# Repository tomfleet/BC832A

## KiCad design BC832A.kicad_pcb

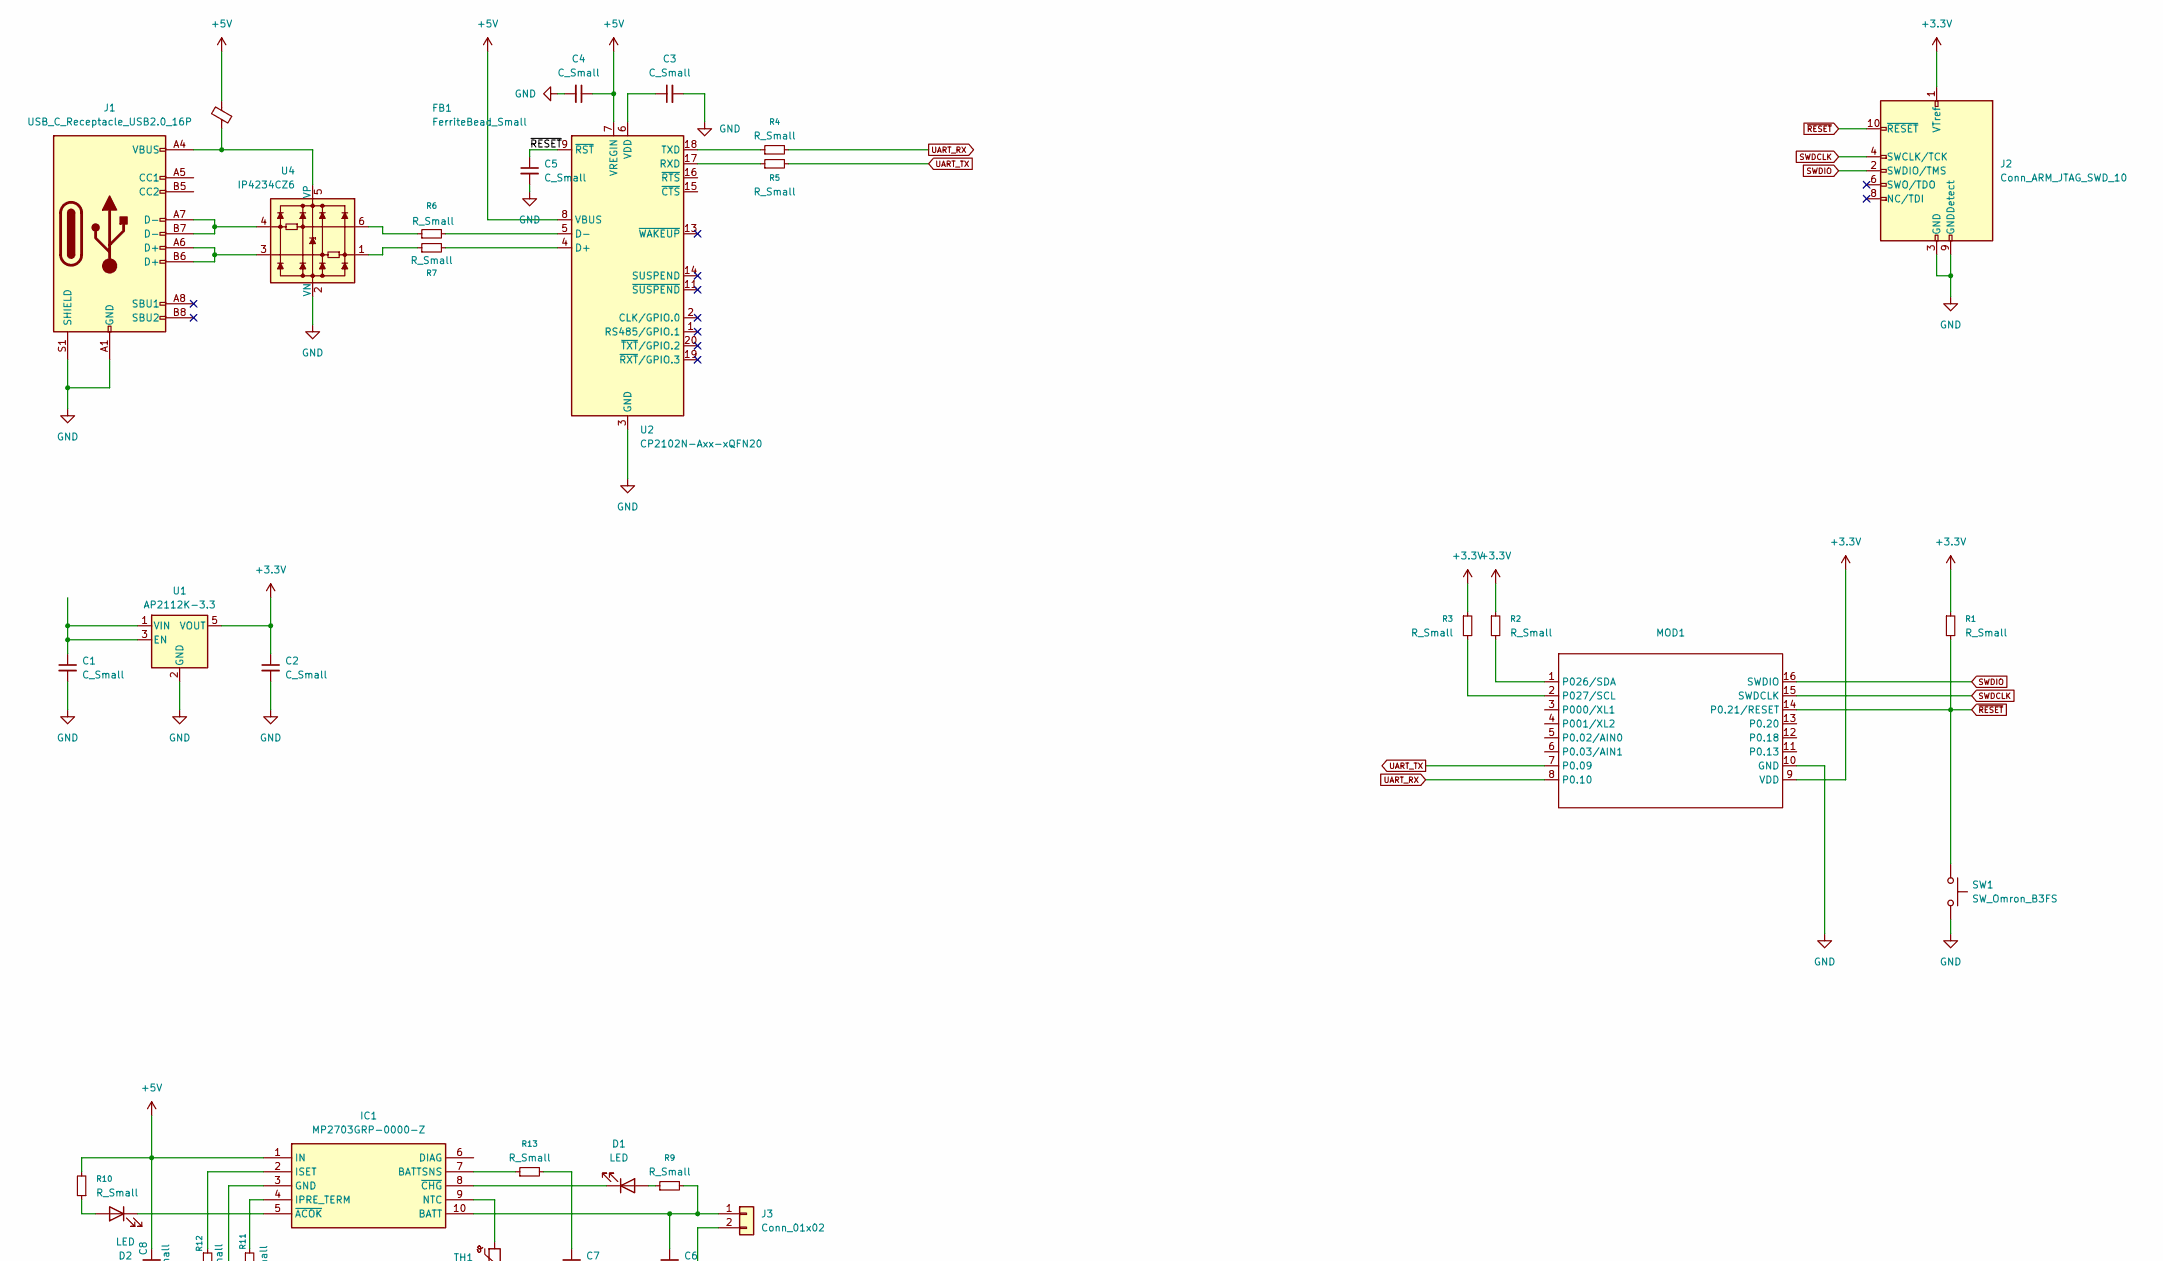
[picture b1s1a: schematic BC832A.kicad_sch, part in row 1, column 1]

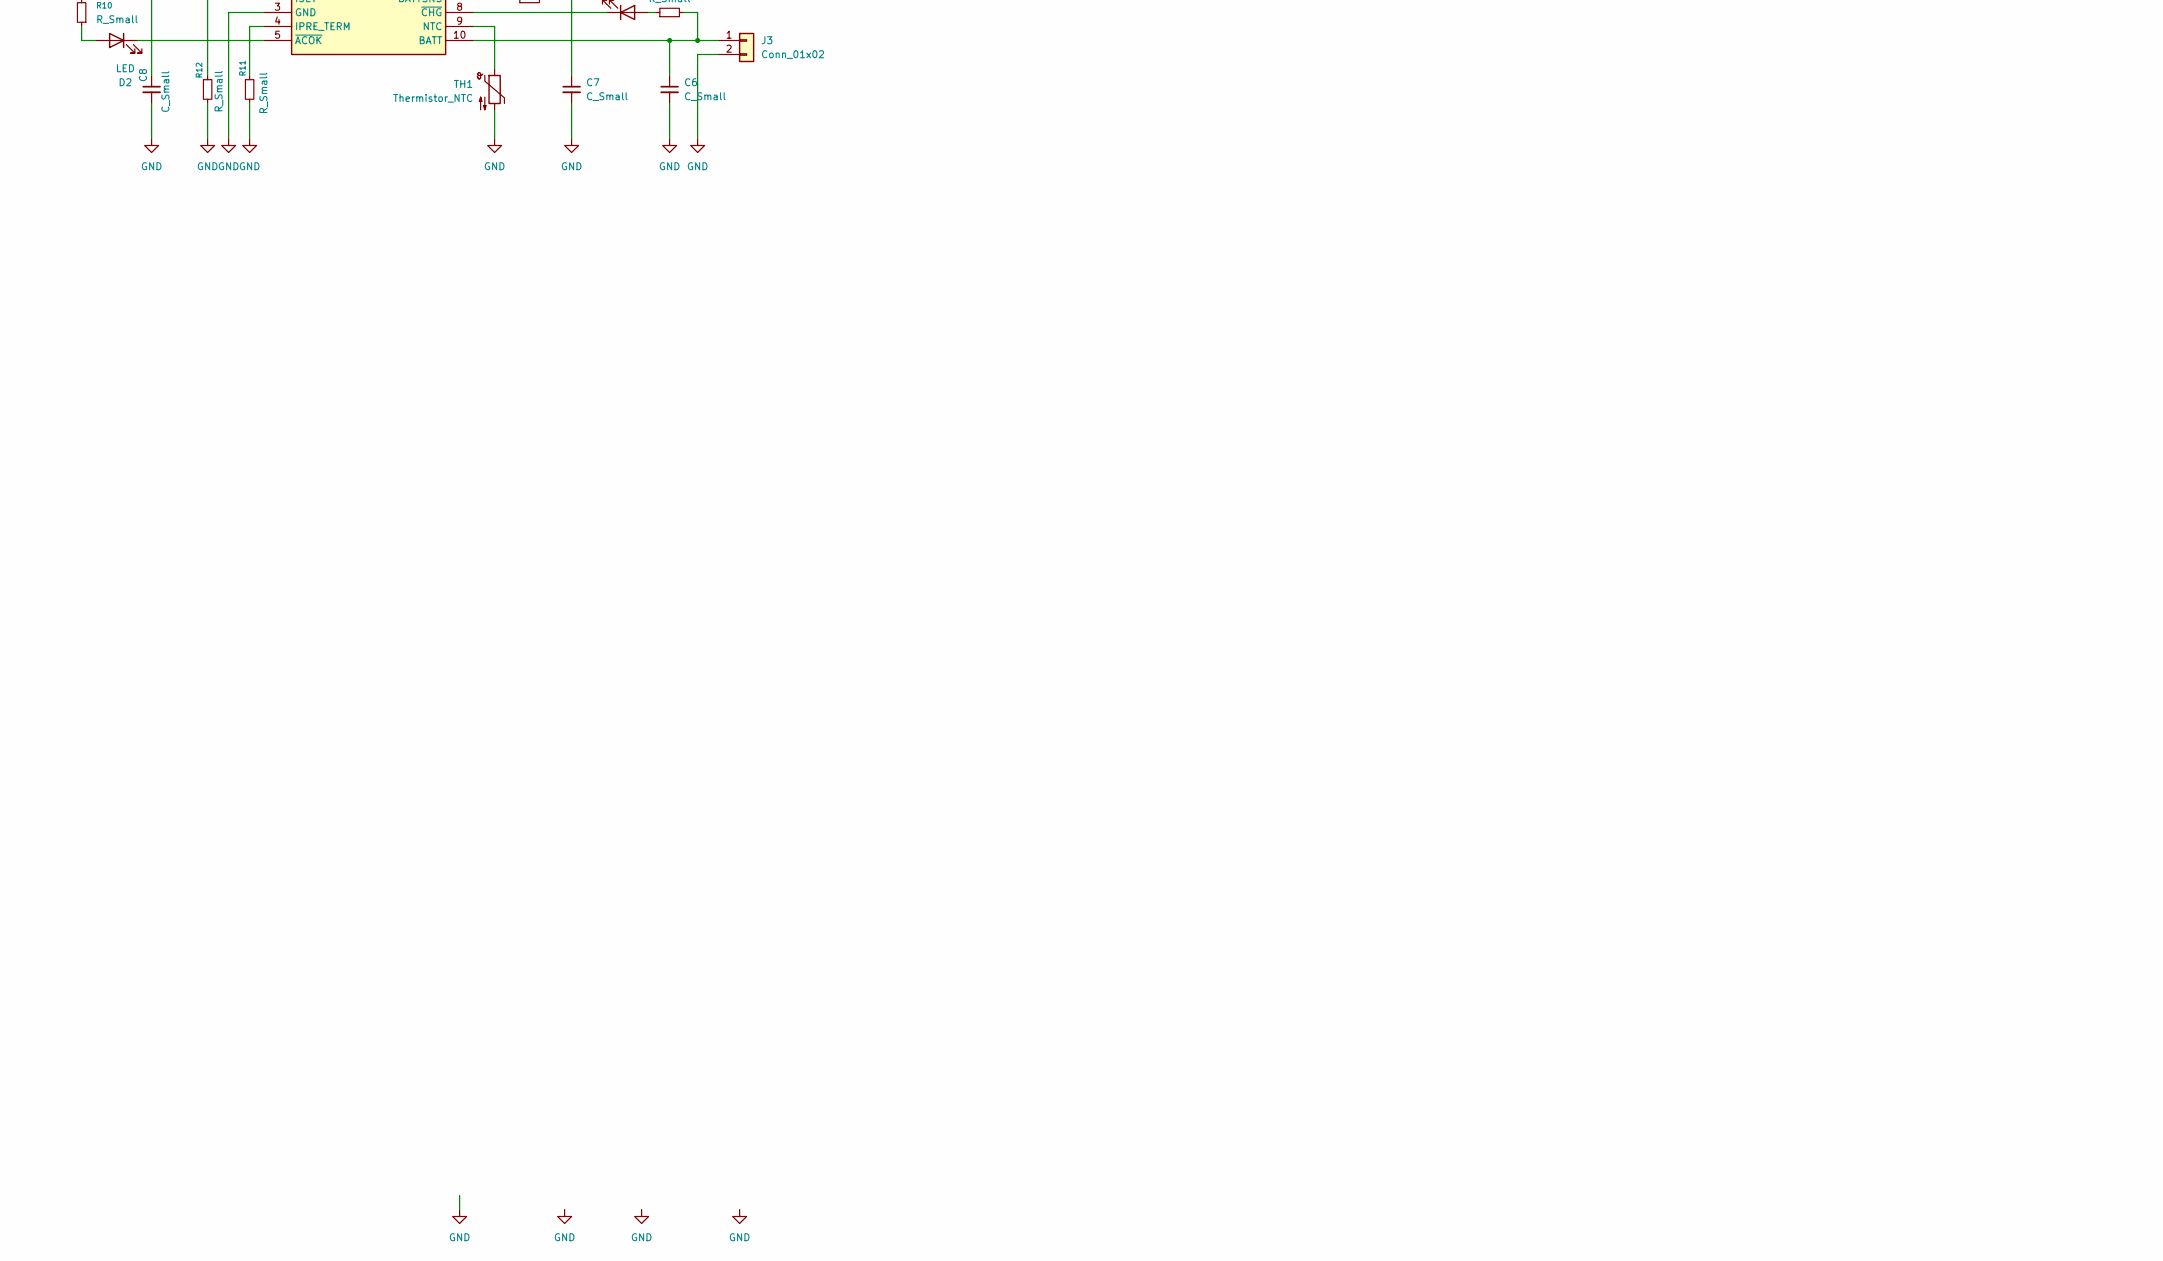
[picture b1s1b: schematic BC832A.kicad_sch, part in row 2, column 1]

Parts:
C1, C2, C3, C4, C5, C6, C7, C8: C_Small; C_0402_1005Metric
D1, D2: LED; LED_0402_1005Metric_Pad0.77x0.64mm_HandSolder
FB1: FerriteBead_Small; L_0603_1608Metric_Pad1.05x0.95mm_HandSolder
IC1: MP2703GRP-0000-Z; MP2703GRP0000Z; Manufacturer_Part_Number MP2703GRP-0000-Z
J1: USB_C_Receptacle_USB2.0_16P; USB_C_Receptacle_GCT_USB4105-xx-A_16P_TopMnt_Horizontal
J2: Conn_ARM_JTAG_SWD_10; PinHeader_2x05_P1.27mm_Vertical_SMD
J3: Conn_01x02; PinHeader_1x02_P1.27mm_Vertical
MOD1: bt832a_simple
R1, R2, R3, R4, R5, R6, R7, R9, R10, R11, R12, R13: R_Small; R_0402_1005Metric_Pad0.72x0.64mm_HandSolder
SW1: SW_Omron_B3FS; SW_Push_1P1T_NO_CK_KMR2
TH1: Thermistor_NTC
U1: AP2112K-3.3; SOT-23-5
U2: CP2102N-Axx-xQFN20; QFN-20-1EP_3x3mm_P0.4mm_EP1.65x1.65mm
U4: IP4234CZ6; SC-74-6_1.55x2.9mm_P0.95mm

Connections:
+3.3V: C2.1, J2.1 (VTref), MOD1.9 (VDD), R1.1, R2.1, R3.1, U1.5 (VOUT)
+5V: C4.1, C8.1, FB1.2, IC1.1 (IN), R10.2, U2.7 (VREGIN), U2.8 (VBUS)
GND: C1.2, C2.2, C3.2, C4.2, C5.2, C6.2, C7.2, C8.2, IC1.3 (GND), J1.A1 (GND), J1.A12 (GND), J1.B1 (GND), J1.B12 (GND), J1.S1 (SHIELD), J2.3 (GND), J2.5 (GND), J2.9 (GNDDetect), J3.2, MOD1.10 (GND), R11.2, R12.2, SW1.2, TH1.2, U1.2 (GND), U2.3 (GND), U2.12 (GND), U2.21 (GND), U4.2 (VN)
unnamed: C7.1, R13.2
unnamed: D1.2 (A), R9.1
unnamed: D1.1 (K), IC1.8 (~CHG)
unnamed: D2.2 (A), R10.1
unnamed: D2.1 (K), IC1.5 (~ACOK)
unnamed: C6.1, IC1.10 (BATT), J3.1, R9.2
unnamed: IC1.7 (BATTSNS), R13.1
unnamed: IC1.4 (IPRE_TERM), R11.1
unnamed: IC1.2 (ISET), R12.1
unnamed: IC1.9 (NTC), TH1.1
unnamed: J1.A6 (D+), J1.B6 (D+), U4.3
unnamed: J1.A7 (D-), J1.B7 (D-), U4.4
unnamed: MOD1.1 (P026/SDA), R2.2
unnamed: MOD1.2 (P027/SCL), R3.2
unnamed: R6.1, U4.6
unnamed: R7.1, U4.1
unnamed: C1.1, U1.1 (VIN), U1.3 (EN)
unnamed: R7.2, U2.4 (D+)
unnamed: R6.2, U2.5 (D-)
unnamed: R5.1, U2.17 (RXD)
unnamed: R4.1, U2.18 (TXD)
unnamed: C3.1, U2.6 (VDD)
unnamed: FB1.1, J1.A4 (VBUS), J1.A9 (VBUS), J1.B4 (VBUS), J1.B9 (VBUS), U4.5 (VP)
SWDCLK: J2.4 (SWCLK/TCK), MOD1.15 (SWDCLK)
SWDIO: J2.2 (SWDIO/TMS), MOD1.16 (SWDIO)
UART_RX: MOD1.8 (P0.10), R4.2
UART_TX: MOD1.7 (P0.09), R5.2
~RESET: C5.1, J2.10 (~RESET), MOD1.14 (P0.21/RESET), R1.2, SW1.1, U2.9 (~RST)

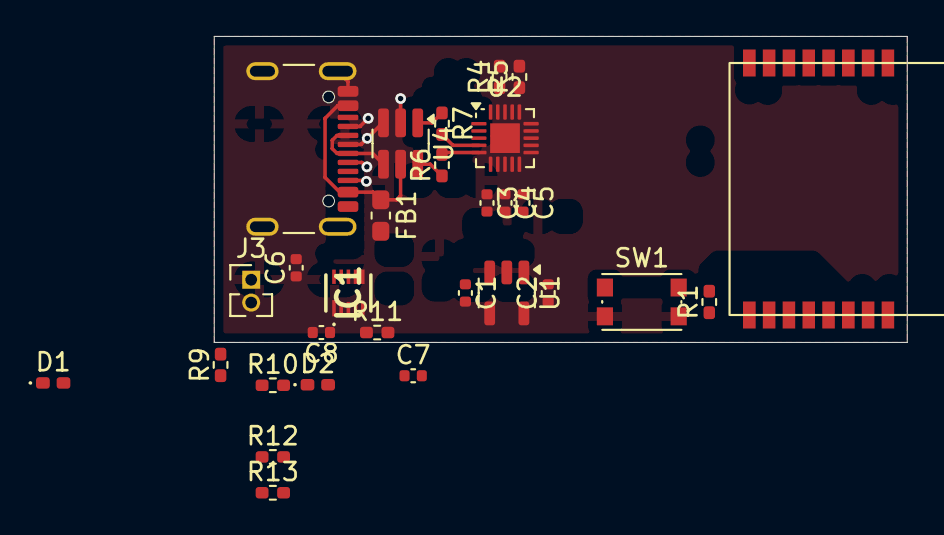
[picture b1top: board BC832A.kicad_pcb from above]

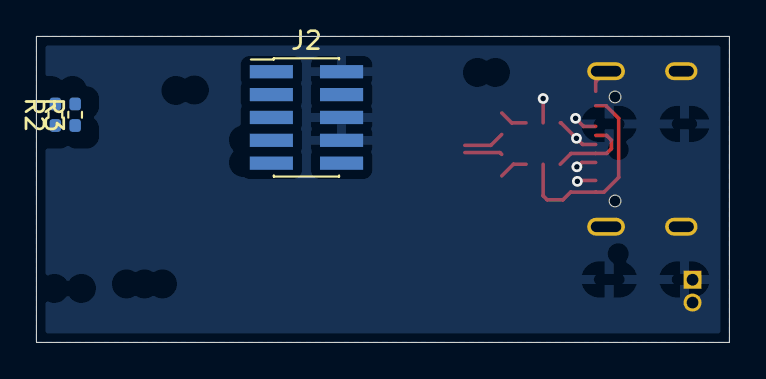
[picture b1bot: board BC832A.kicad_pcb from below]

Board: 4 copper layers, 38.5 x 17.0 mm, 32 parts (3 on the bottom side), 30 nets.

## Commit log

2025-06-17 Create .gitignore
    gitignore
